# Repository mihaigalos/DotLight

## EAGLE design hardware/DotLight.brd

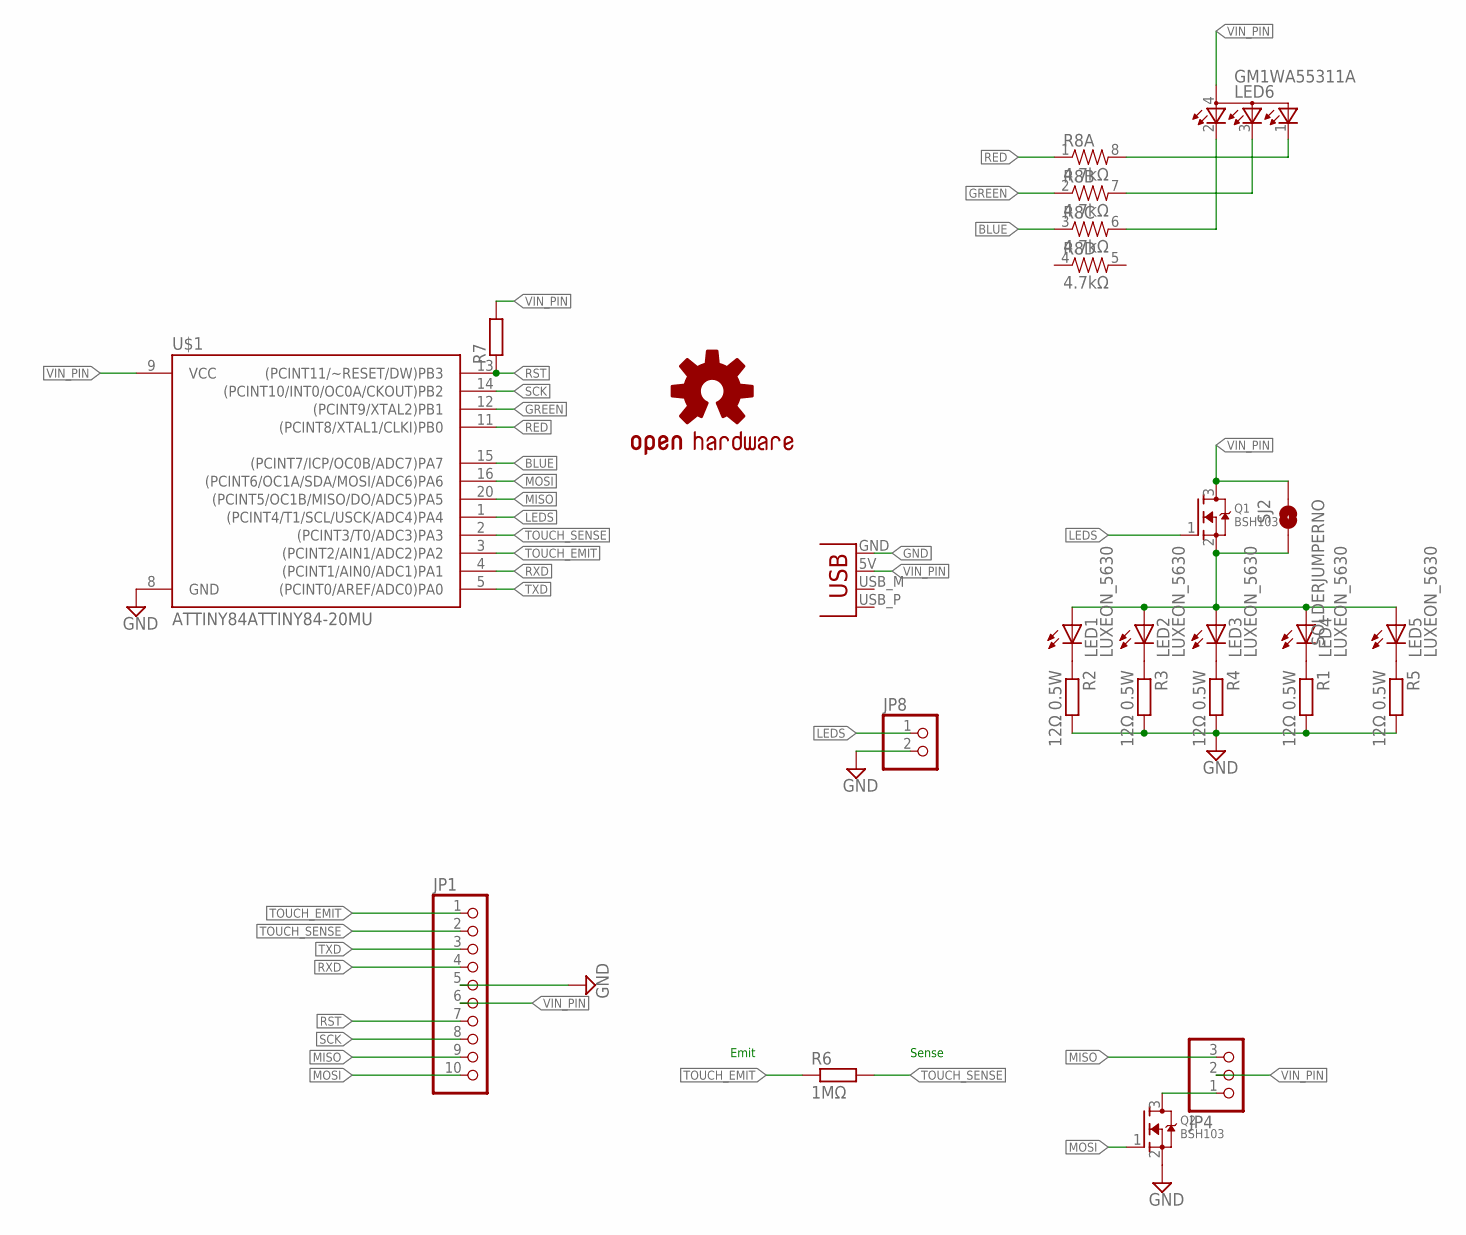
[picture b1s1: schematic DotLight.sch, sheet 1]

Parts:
JP1: PINHD-1X10; 1X10
JP3: USBPCB; USB-A-PCB
JP4: PINHD-1X3; 1X03
JP8: PINHD-1X2; 1X02
LED1, LED2, LED3, LED4, LED5: LUXEON_5630
LED6: GM1WA55311A
LOGO1: OSHW-LOGOS; OSHW-LOGO-S
Q1, Q2: BSH103; SOT23
R1, R2, R3, R4, R5: 12Ω 0.5W; R1210
R6: 1MΩ; R1206
R7: R-EU_R0603; R0603
R8: 4.7kΩ; 0603-ARV
SJ2: SOLDERJUMPERNO; SJ_2S-NO
U$1: ATTINY84ATTINY84-20MU; QFN20

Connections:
BLUE: R8.3 (1), U$1.15 ((PCINT7/ICP/OC0B/ADC7)PA7)
GND: JP1.5, JP3.GND, JP8.2, Q2.2 (S), R1.2, R2.2, R3.2, R4.2, R5.2, U$1.8 (GND)
GO: LED1.A, LED2.A, LED3.A, LED4.A, LED5.A, Q1.2 (S), SJ2.2
GREEN: R8.2 (1), U$1.12 ((PCINT9/XTAL2)PB1)
LEDS: JP8.1, Q1.1 (G), U$1.1 ((PCINT4/T1/SCL/USCK/ADC4)PA4)
LED_R1: LED4.C, R1.1
LED_R2: LED1.C, R2.1
LED_R3: LED2.C, R3.1
LED_R4: LED3.C, R4.1
LED_R5: LED5.C, R5.1
MISO: JP1.9, JP4.3, U$1.20 ((PCINT5/OC1B/MISO/DO/ADC5)PA5)
MOSI: JP1.10, Q2.1 (G), U$1.16 ((PCINT6/OC1A/SDA/MOSI/ADC6)PA6)
unnamed: LED6.2 (CRED), R8.6 (2)
unnamed: LED6.3 (CBLUE), R8.7 (2)
unnamed: JP4.1, Q2.3 (D)
unnamed: LED6.1 (CGREEN), R8.8 (2)
RED: R8.1, U$1.11 ((PCINT8/XTAL1/CLKI)PB0)
RST: JP1.7, R7.1, U$1.13 ((PCINT11/~RESET/DW)PB3)
RXD: JP1.4, U$1.4 ((PCINT1/AIN0/ADC1)PA1)
SCK: JP1.8, U$1.14 ((PCINT10/INT0/OC0A/CKOUT)PB2)
TOUCH_EMIT: JP1.1, R6.1, U$1.3 ((PCINT2/AIN1/ADC2)PA2)
TOUCH_SENSE: JP1.2, R6.2, U$1.2 ((PCINT3/T0/ADC3)PA3)
TXD: JP1.3, U$1.5 ((PCINT0/AREF/ADC0)PA0)
VIN_PIN: JP1.6, JP3.5V (VBUS), JP4.2, LED6.4 (A), Q1.3 (D), R7.2, SJ2.1, U$1.9 (VCC)

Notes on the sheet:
Emit
Sense

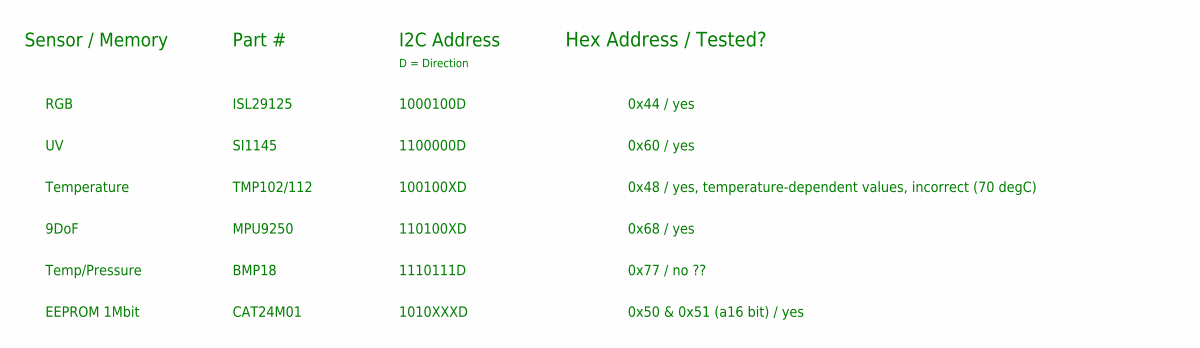
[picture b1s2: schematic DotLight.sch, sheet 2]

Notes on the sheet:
Sensor / Memory
Part #
I2C Address
RGB
ISL29125
1000100D
SI1145
1100000D
Temperature
TMP102/112
100100XD
9DoF
MPU9250
110100XD
Hex Address / Tested?
0x44 / yes
0x60 / yes
Temp/Pressure
BMP18
1110111D
0x77 / no ??
0x48 / yes, temperature-dependent values, incorrect (70 degC)
EEPROM 1Mbit
CAT24M01
1010XXXD
0x50 & 0x51 (a16 bit) / yes
D = Direction
0x68 / yes

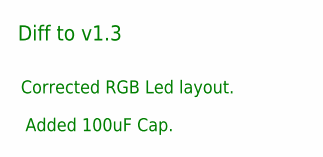
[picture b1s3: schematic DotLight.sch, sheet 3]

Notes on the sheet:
Diff to v1.3
Corrected RGB Led layout.
Added 100uF Cap.

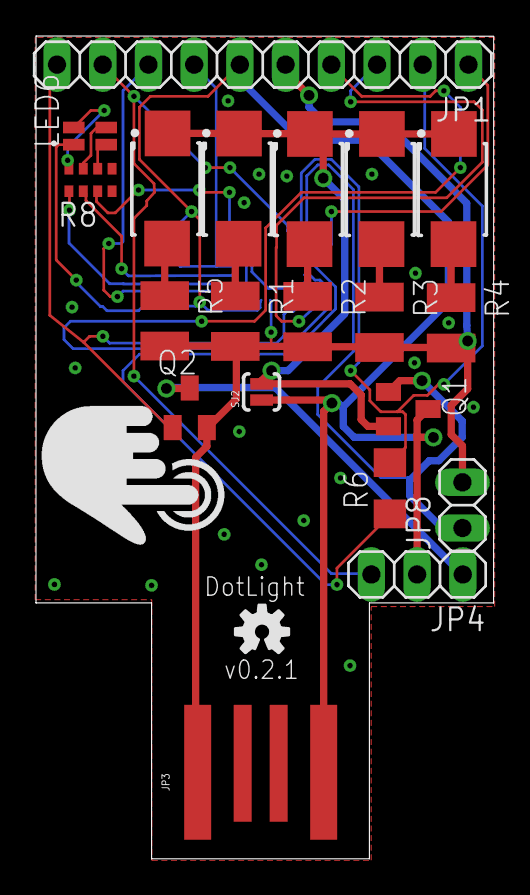
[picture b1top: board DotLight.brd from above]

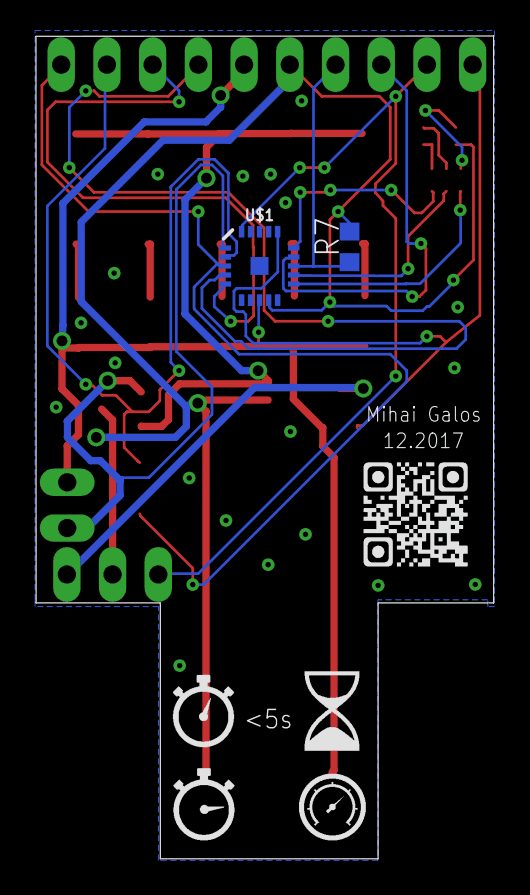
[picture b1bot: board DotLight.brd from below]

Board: 2 copper layers, 25.4 x 45.7 mm, 23 parts (2 on the bottom side), 24 nets.

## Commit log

2017-10-07 Mirror parts for space for PIR
2017-10-07 Adjust solderjumpers
2017-10-22 Add QR logo
2017-10-23 Add Attiny85 and usage logos
2017-10-24 v0.2.0
2017-10-24 v0.2.1
2017-10-24 Add RGB led
2017-10-24 Rearrange logos
2017-10-24 Add R to RGB
2017-10-25 Correct RGB 3V3
2017-11-05 Insert warning : using t84 instad of t85

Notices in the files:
parts and their libraries:
HighPowerLed: Lumileds 5630 Datasheet DS201 20130228 ©2013 Philips Lumileds Lighting Company.
Particle-Devices: Licensing: Designed by Particle.
SparkFun-Retired: Licensing: Creative Commons ShareAlike 4.0 International - https://creativecommons.org/licenses/by-sa/4.0
